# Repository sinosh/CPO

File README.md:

# CPO
Code Practice Oscillator

Kicad files for Code Practice oscillator, Twin T Oscillator and an LM386 amp

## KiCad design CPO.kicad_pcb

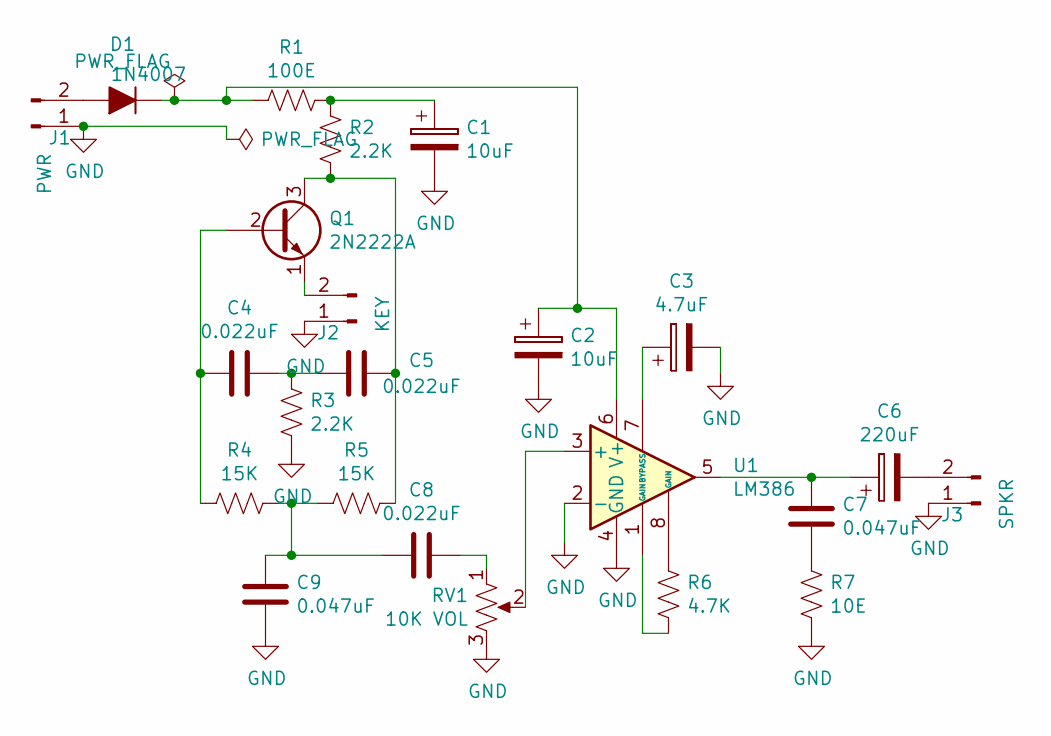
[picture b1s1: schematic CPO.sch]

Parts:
C1, C2: 10uF; CP_Radial_D5.0mm_P2.50mm
C3: 4.7uF; CP_Radial_D5.0mm_P2.50mm
C4, C5, C8: 0.022uF; C_Disc_D3.8mm_W2.6mm_P2.50mm
C6: 220uF; CP_Radial_D10.0mm_P2.50mm_P5.00mm
C7, C9: 0.047uF; C_Disc_D3.8mm_W2.6mm_P2.50mm
D1: 1N4007; D_DO-34_SOD68_P7.62mm_Horizontal
J1: PWR; SolderWirePad_1x02_P3.81mm_Drill1mm
J2: KEY; SolderWirePad_1x02_P3.81mm_Drill1mm
J3: SPKR; SolderWirePad_1x02_P3.81mm_Drill1mm
Q1: 2N2222A; TO-92L_Inline_Wide
R1: 100E; R_Axial_DIN0207_L6.3mm_D2.5mm_P10.16mm_Horizontal
R2, R3: 2.2K; R_Axial_DIN0207_L6.3mm_D2.5mm_P10.16mm_Horizontal
R4, R5: 15K; R_Axial_DIN0207_L6.3mm_D2.5mm_P10.16mm_Horizontal
R6: 4.7K; R_Axial_DIN0207_L6.3mm_D2.5mm_P10.16mm_Horizontal
R7: 10E; R_Axial_DIN0207_L6.3mm_D2.5mm_P10.16mm_Horizontal
RV1: 10K VOL; Potentiometer_Bourns_3266Y_Vertical
U1: LM386; DIP-8_W7.62mm_LongPads

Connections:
GND: C1.2, C2.2, C3.2, C9.1, J1.1, J2.1, J3.1, R3.2, R7.1, RV1.3, U1.2 (-), U1.4 (GND)
unnamed: C1.1, R1.2, R2.2
unnamed: C2.1, D1.1 (K), R1.1, U1.6 (V+)
unnamed: C3.1, U1.7 (BYPASS)
unnamed: C4.1, C5.2, R3.1
unnamed: C4.2, Q1.2 (B), R4.2
unnamed: C5.1, Q1.3 (C), R2.1, R5.1
unnamed: C6.1, C7.1, U1.5
unnamed: C6.2, J3.2
unnamed: C7.2, R7.2
unnamed: C8.1, RV1.1
unnamed: C8.2, C9.2, R4.1, R5.2
unnamed: D1.2 (A), J1.2
unnamed: J2.2, Q1.1 (E)
unnamed: R6.1, U1.1 (GAIN)
unnamed: R6.2, U1.8 (GAIN)
unnamed: RV1.2, U1.3 (+)

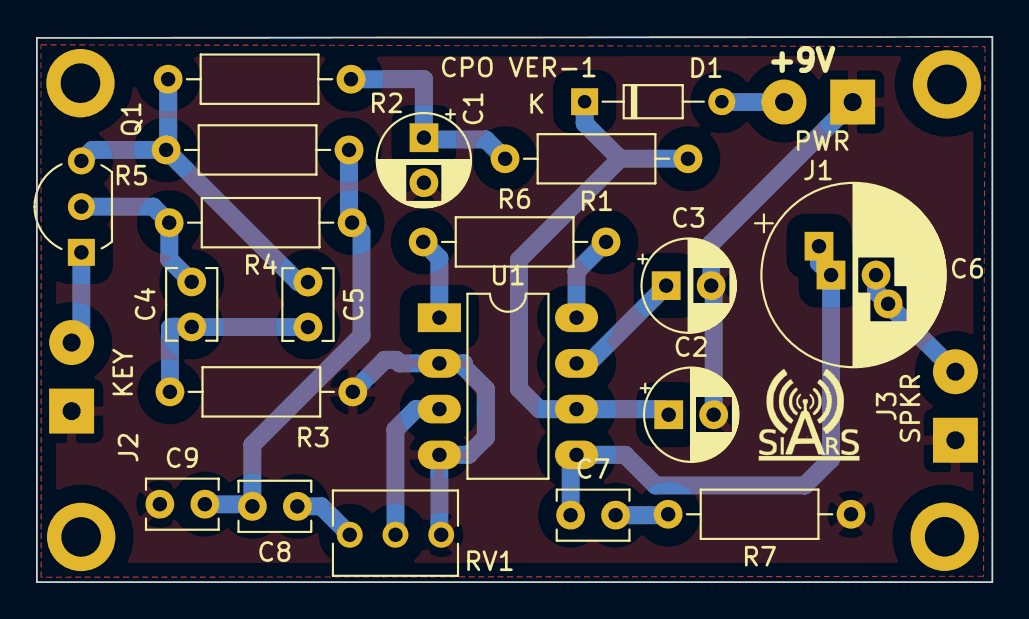
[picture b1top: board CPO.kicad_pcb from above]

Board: 2 copper layers, 53.1 x 30.3 mm, 27 parts (0 on the bottom side), 17 nets.

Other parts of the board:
M2, M2#2, M2#3, M2#4: M2; MountingHole_2.2mm_M2_DIN965_Pad
